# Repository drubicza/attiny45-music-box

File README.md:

# attiny45-music-box

ATtiny45 music box based on elm-chan's tutorial. For more information, please visit [elm-chan's website](http://elm-chan.org/works/mxb/report.html)

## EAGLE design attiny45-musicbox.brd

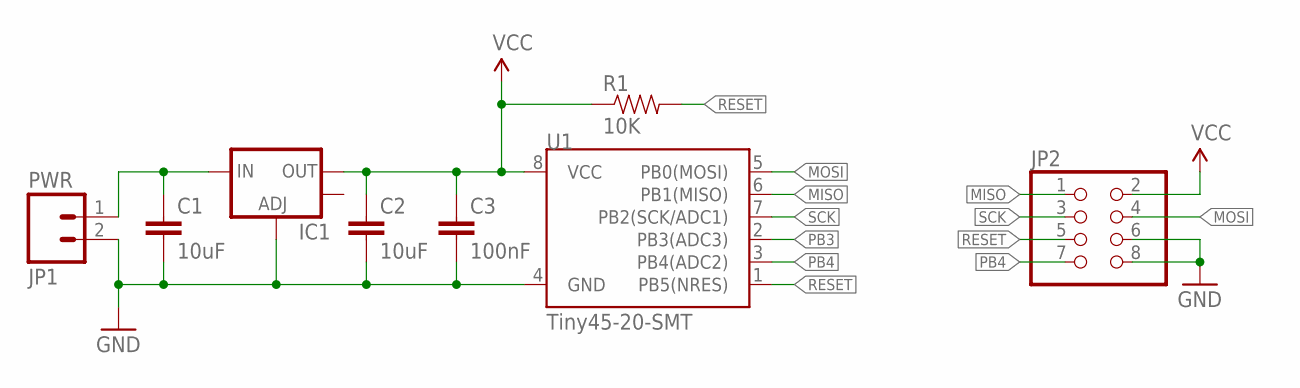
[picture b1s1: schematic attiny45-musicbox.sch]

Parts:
C1, C2: 10uF; 0805
C3: 100nF; 0805
IC1: V_REG_LM1117SOT223; SOT223
JP1: PWR; 1X02
JP2: PINHD-2X4; 2X04
R1: 10K; 0603-RES
U1: Tiny45-20-SMT; SO08-EIAJ

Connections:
GND: C1.2, C2.2, C3.2, IC1.1 (ADJ), JP1.2, JP2.6, JP2.8, U1.4 (GND)
MISO: JP2.1, U1.6 (PB1(MISO))
MOSI: JP2.4, U1.5 (PB0(MOSI))
unnamed: C1.1, IC1.3 (IN), JP1.1
PB3: U1.2 (PB3(ADC3))
PB4: JP2.7, U1.3 (PB4(ADC2))
RESET: JP2.5, R1.2, U1.1 (PB5(NRES))
SCK: JP2.3, U1.7 (PB2(SCK/ADC1))
VCC: C2.1, C3.1, IC1.2 (OUT), JP2.2, R1.1, U1.8 (VCC)

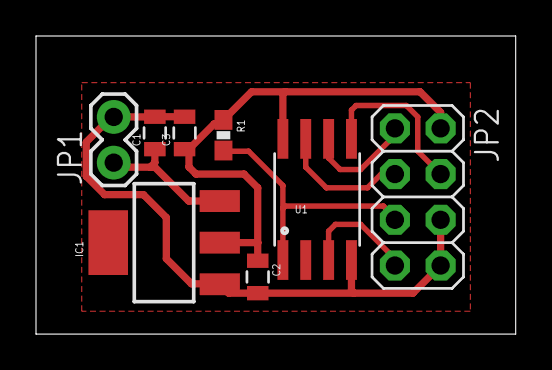
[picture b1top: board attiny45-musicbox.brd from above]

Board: 2 copper layers, 26.6 x 16.6 mm, 8 parts (0 on the bottom side), 8 nets.

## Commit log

2015-02-23 :new: Initial commit

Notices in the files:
parts and their libraries:
SparkFun-Capacitors: Licensing: Creative Commons ShareAlike 4.0 International - https://creativecommons.org/licenses/by-sa/4.0
